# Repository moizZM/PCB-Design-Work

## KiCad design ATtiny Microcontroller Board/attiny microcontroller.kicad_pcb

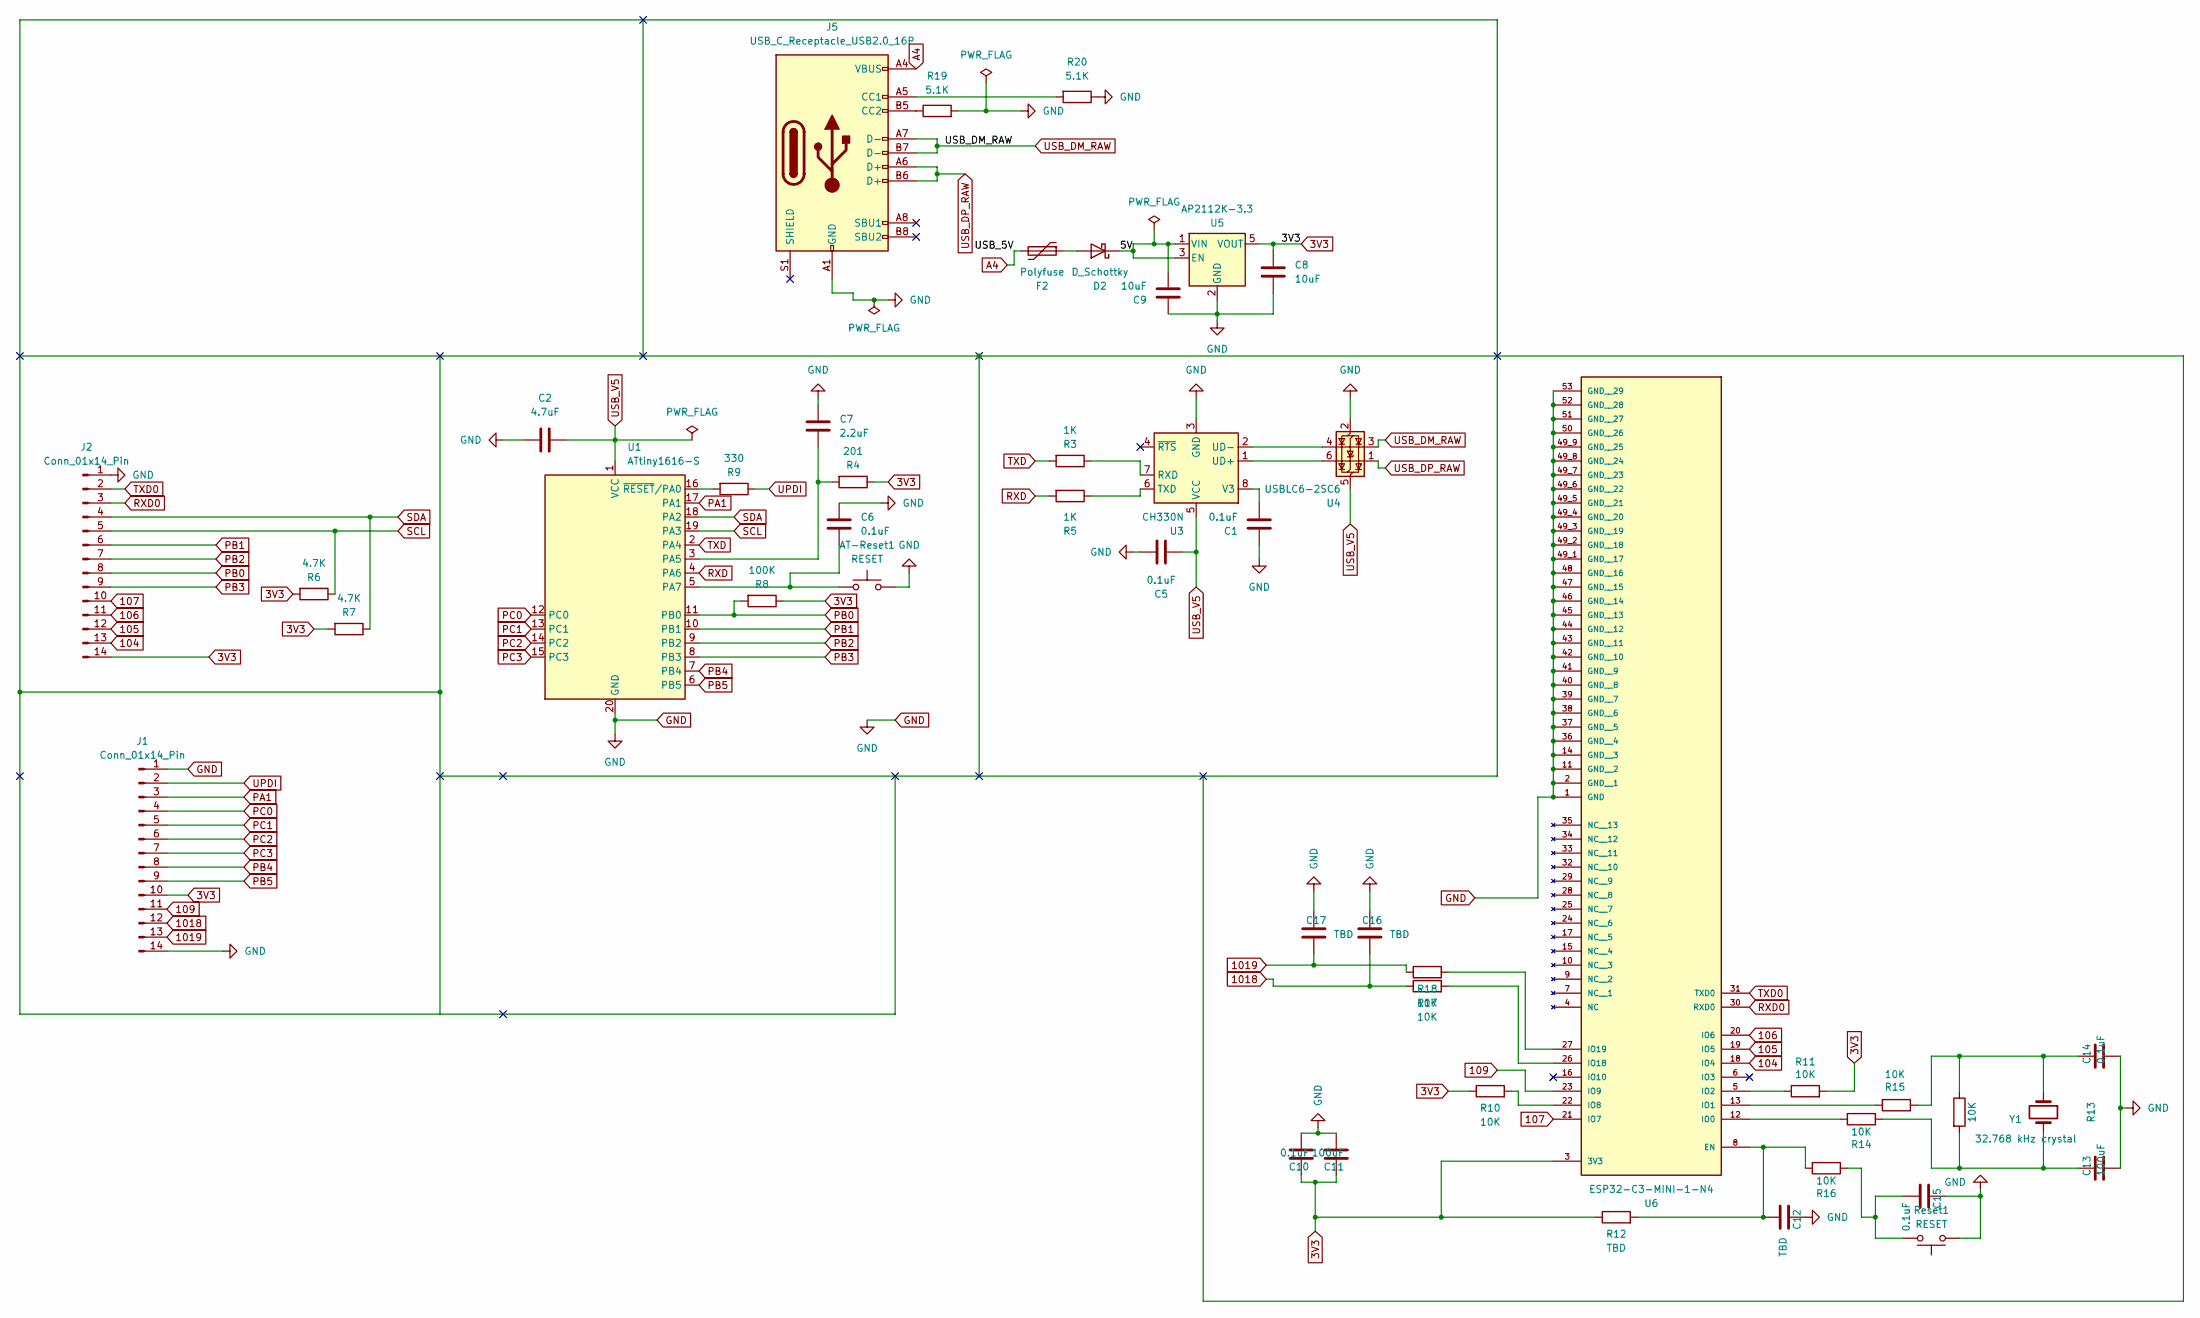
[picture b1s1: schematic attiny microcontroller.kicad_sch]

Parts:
AT-Reset1: RESET; SW_Push_SPST_NO_Alps_SKRK
C1, C5, C6, C10, C14, C15: 0.1uF; C_0201_0603Metric_Pad0.64x0.40mm_HandSolder
C2: 4.7uF; C_0201_0603Metric_Pad0.64x0.40mm_HandSolder
C7: 2.2uF; C_0201_0603Metric_Pad0.64x0.40mm_HandSolder
C8, C9: 10uF; C_0201_0603Metric_Pad0.64x0.40mm_HandSolder
C11, C13: 100uF; C_0201_0603Metric_Pad0.64x0.40mm_HandSolder
C12, C16, C17: TBD; C_0201_0603Metric_Pad0.64x0.40mm_HandSolder
D2: D_Schottky; D_2114_3652Metric
F2: Polyfuse; FUSE_MF-SM030-2_BRN
J1, J2: Conn_01x14_Pin; PinHeader_1x14_P1.00mm_Vertical
J5: USB_C_Receptacle_USB2.0_16P; USB_C_Receptacle_GCT_USB4110
R3, R5: 1K; R_0201_0603Metric
R4: 201; R_0201_0603Metric
R6, R7: 4.7K; R_0201_0603Metric
R8: 100K; R_0201_0603Metric
R9: 330; R_0201_0603Metric
R10, R11, R13, R14, R15, R16, R17, R18: 10K; R_0201_0603Metric
R12: TBD; C_0201_0603Metric_Pad0.64x0.40mm_HandSolder
R19, R20: 5.1K; R_0201_0603Metric
Reset1: RESET; SW_Push_SPST_NO_Alps_SKRK
U1: ATtiny1616-S; SOIC-20W_7.5x12.8mm_P1.27mm
U3: CH330N; SOIC-8_3.9x4.9mm_P1.27mm
U4: USBLC6-2SC6; SOT-23-6
U5: AP2112K-3.3; SOT-23-5
U6: ESP32-C3-MINI-1-N4; XCVR_ESP32-C3-MINI-1-N4; PARTREV v1.0
Y1: 32.768 kHz crystal; Crystal_SMD_3215-2Pin_3.2x1.5mm

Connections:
3V3: C8.1, C10.2, C11.2, J1.10, J2.14, R4.1, R6.2, R7.2, R8.1, R10.1, R11.2, R12.1, U5.5 (VOUT), U6.3 (3V3)
104: J2.13, U6.18 (IO4)
105: J2.12, U6.19 (IO5)
106: J2.11, U6.20 (IO6)
107: J2.10, U6.21 (IO7)
109: J1.11, U6.23 (IO9)
1018: C16.1, J1.12, R17.1
1019: C17.1, J1.13, R18.1
/5V: C9.2, D2.1 (K), U5.1 (VIN), U5.3 (EN)
A4: F2.2, J5.A4 (VBUS), J5.A9 (VBUS), J5.B4 (VBUS), J5.B9 (VBUS)
GND: AT-Reset1.2, C1.1, C2.2, C5.1, C6.2, C7.2, C8.2, C9.1, C10.1, C11.1, C12.2, C13.1, C14.1, C15.2, C16.2, C17.2, J1.1, J1.14, J2.1, J5.A1 (GND), J5.A12 (GND), J5.B1 (GND), J5.B12 (GND), R19.2, R20.1, Reset1.1, U1.20 (GND), U3.3 (GND), U4.2 (GND), U5.2 (GND), U6.1 (GND), U6.2 (GND__1), U6.11 (GND__2), U6.14 (GND__3), U6.36 (GND__4), U6.37 (GND__5), U6.38 (GND__6), U6.39 (GND__7), U6.40 (GND__8), U6.41 (GND__9), U6.42 (GND__10), U6.43 (GND__11), U6.44 (GND__12), U6.45 (GND__13), U6.46 (GND__14), U6.47 (GND__15), U6.48 (GND__16), U6.49_1 (GND__17), U6.49_2 (GND__18), U6.49_3 (GND__19), U6.49_4 (GND__20), U6.49_5 (GND__21), U6.49_6 (GND__22), U6.49_7 (GND__23), U6.49_8 (GND__24), U6.49_9 (GND__25), U6.50 (GND__26), U6.51 (GND__27), U6.52 (GND__28), U6.53 (GND__29); also elsewhere on the board
unnamed: C13.2, R13.2, R14.1, Y1.2
unnamed: C14.2, R13.1, R15.1, Y1.1
unnamed 13: C15.1, R16.1, Reset1.2; also elsewhere on the board
unnamed: D2.2 (A), F2.1
unnamed: J5.A5 (CC1), R20.2
unnamed: J5.B5 (CC2), R19.1
unnamed: C7.1, R4.2, U1.3 (PA5)
unnamed 18: AT-Reset1.1, C6.1, U1.5 (PA7); also elsewhere on the board
unnamed: R9.2, U1.16 (~RESET/PA0)
unnamed: R3.1, U3.7 (RXD)
unnamed: R5.1, U3.6 (TXD)
unnamed: U3.1 (UD+), U4.6 (I/O1)
unnamed: U3.2 (UD-), U4.4 (I/O2)
unnamed: C1.2, U3.8 (V3)
unnamed: C12.1, R12.2, R16.2, U6.8 (EN)
unnamed: R14.2, U6.12 (IO0)
unnamed: R15.2, U6.13 (IO1)
unnamed: R11.1, U6.5 (IO2)
unnamed: R10.2, U6.22 (IO8)
unnamed: R17.2, U6.26 (IO18)
unnamed: R18.2, U6.27 (IO19)
PA1: J1.3, U1.17 (PA1)
PB0: J2.8, R8.2, U1.11 (PB0)
PB1: J2.6, U1.10 (PB1)
PB2: J2.7, U1.9 (PB2)
PB3: J2.9, U1.8 (PB3)
PB4: J1.8, U1.7 (PB4)
PB5: J1.9, U1.6 (PB5)
PC0: J1.4, U1.12 (PC0)
PC1: J1.5, U1.13 (PC1)
PC2: J1.6, U1.14 (PC2)
PC3: J1.7, U1.15 (PC3)
RXD: R5.2, U1.4 (PA6)
RXD0: J2.3, U6.30 (RXD0)
SCL: J2.5, R6.1, U1.19 (PA3)
SDA: J2.4, R7.1, U1.18 (PA2)
TXD: R3.2, U1.2 (PA4)
TXD0: J2.2, U6.31 (TXD0)
UPDI: J1.2, R9.1
USB_DM_RAW: J5.A7 (D-), J5.B7 (D-), U4.3 (I/O2)
USB_DP_RAW: J5.A6 (D+), J5.B6 (D+), U4.1 (I/O1)
USB_V5: C2.1, C5.2, U1.1 (VCC), U3.5 (VCC), U4.5 (VBUS)

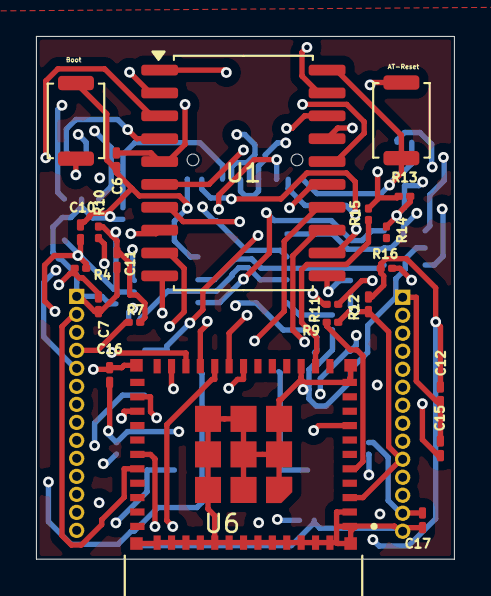
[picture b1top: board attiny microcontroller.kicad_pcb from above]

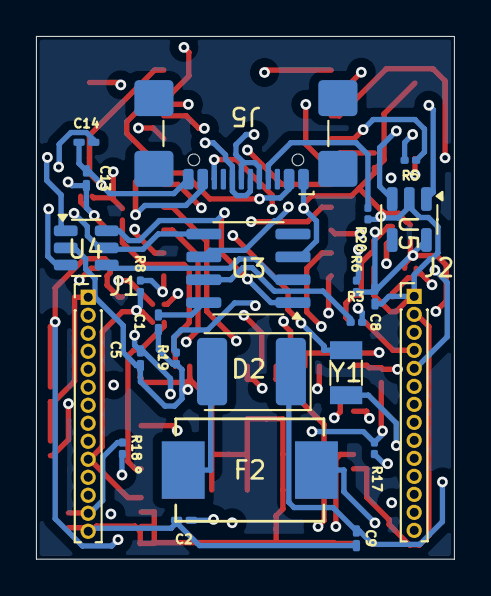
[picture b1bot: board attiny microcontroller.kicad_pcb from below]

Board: 4 copper layers, 23.2 x 29.0 mm, 46 parts (24 on the bottom side), 53 nets.

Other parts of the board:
AT-Reset: RESET; SW_Push_SPST_NO_Alps_SKRK
Boot: RESET; SW_Push_SPST_NO_Alps_SKRK

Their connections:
GND: AT-Reset.2, Boot.1; also elsewhere on the board
unnamed 13: Boot.2; also elsewhere on the board
unnamed 18: AT-Reset.1; also elsewhere on the board

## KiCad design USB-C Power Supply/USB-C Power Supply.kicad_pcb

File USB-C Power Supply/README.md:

# USB-C Power Supply
> 3D  viwe

> Layout

# USB-C Power Supply

## Overview
This project demonstrates the complete design and development of a **USB-C Power Supply** circuit.  
The goal was to create a small PCB that outputs **5 V** through a **USB Type-C** connector using correct CC (Configuration Channel) resistors.  
The board includes a power indicator LED, decoupling capacitors, and is fully ready for **JLCPCB** manufacturing.

---

## What Was Done
- Designed a **schematic** in **KiCad 8.0** for a 5 V USB-C power source.  
- Implemented **CC1** and **CC2 pull-down resistors (5.1 kΩ)** for correct USB-C negotiation.  
- Added **100 nF decoupling capacitor** for voltage stability.  
- Added **LED indicator** with **1 kΩ resistor** for power-on status.  
- Created and annotated all symbols and footprints in KiCad.  
- Designed a **two-layer PCB layout** following **JLCPCB** design rules.  
- Defined **board outline, silkscreen labels, mounting holes**, and reference text.  
- Generated **Gerber**, **Drill**, **BOM**, and **Pick-and-Place** files for fabrication.  
- Verified schematic (ERC) and layout (DRC) before manufacturing.  
- Prepared files for **JLCPCB assembly** and optional 3D-printed enclosure.

---

## Hardware Details
| Parameter | Description |
|------------|-------------|
| **Input** | USB-C Receptacle (VBUS = 5 V) |
| **Output** | 2-Pin Header (5 V / GND) |
| **Resistors** | 5.1 kΩ × 2 (CC1/CC2), 1 kΩ × 1 (LED) |
| **Capacitors** | 100 nF (Decoupling) |
| **Indicator** | Power LED |
| **Board Layers** | 2 |
| **Power** | 5 V @ up to 3 A |
| **Mounting** | 4 × M2 holes |

---

## Project Files
- `USB-C Power Supply.kicad_pro` – KiCad project file  
- `USB-C Power Supply.kicad_sch` – Schematic  
- `USB-C Power Supply.kicad_pcb` – PCB layout  
- `SCH.pdf` – Printable schematic reference  

---

## Manufacturing and Assembly
1. Export **Gerber** and **Drill** files from KiCad.  
2. Upload the ZIP archive to [**JLCPCB**](https://jlcpcb.com).  
3. Choose desired solder-mask and silkscreen colors.  
4. (Optional) Add logo or image for silkscreen layer.  
5. Order boards (with or without assembly) and test after delivery.

---

## Testing
- Connected a USB-C cable from a 5 V adapter.  
- Verified **5 V output** at the terminal header.  
- Observed **LED indicator ON** confirming active power.  
- Ensured no short circuits or trace issues.

---

## Results
The PCB provides a **stable 5 V output**, compact design, and clear labeling.  
It can serve as a reference or base module for **USB-powered embedded projects** or **sensor systems** that need a simple regulated power supply.

---

## Tools Used
- **KiCad 8.0** – Schematic capture and PCB layout  
- **JLCPCB** – PCB manufacturing and assembly  
- **Fusion 360 (optional)** – Enclosure and 3D model design  

---

## Author
**Moiz Zaheer Malik**  
Hochschule Hamm-Lippstadt (HSHL)  
October 2025

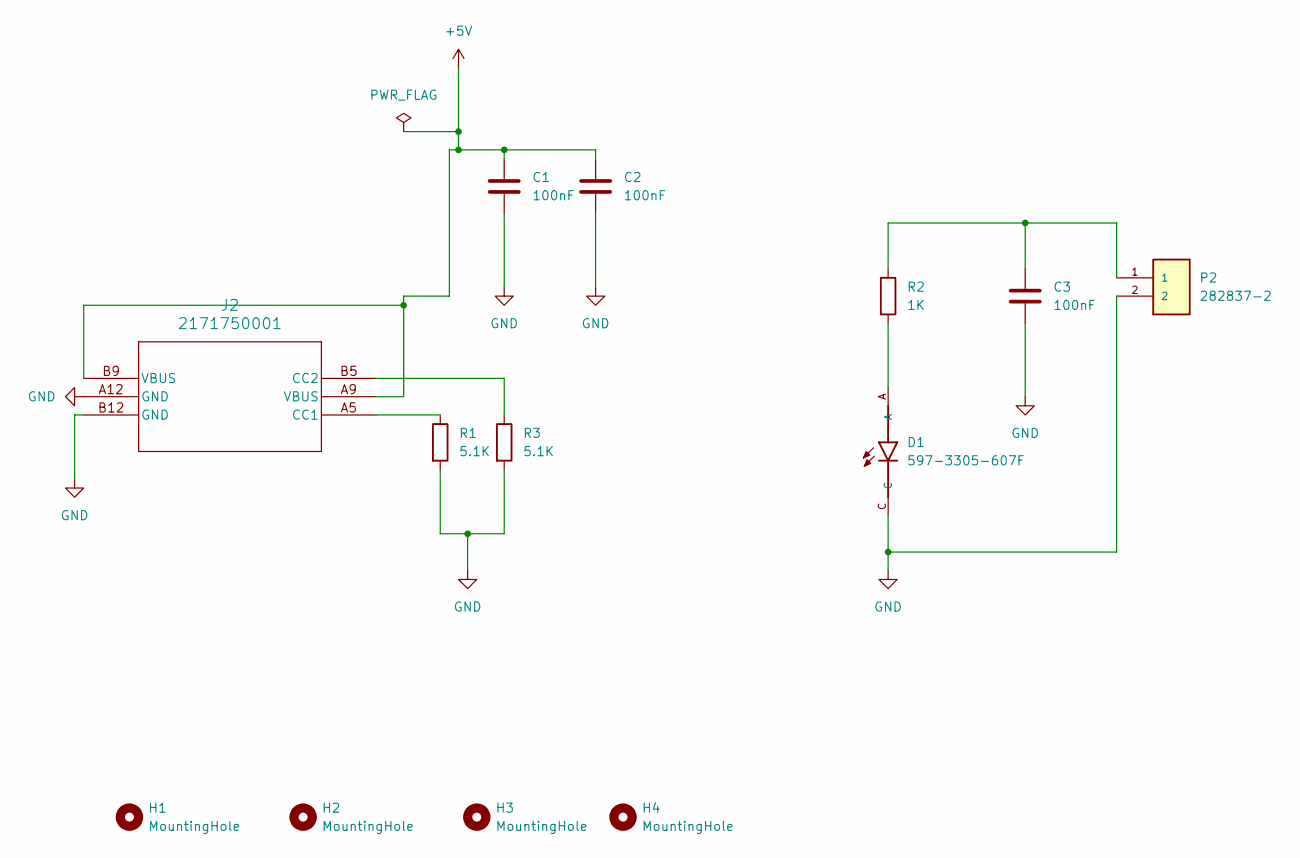
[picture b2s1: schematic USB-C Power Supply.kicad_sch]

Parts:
C1, C2, C3: 100nF; C_0201_0603Metric
D1: 597-3305-607F; LEDC2012X70N
H1, H2, H3, H4: MountingHole; MountingHole_2.2mm_M2_DIN965_Pad
J2: 2171750001; 2171750001_MOL
P2: 282837-2; TE_282837-2; PARTREV G3
R1, R3: 5.1K; R_0201_0603Metric
R2: 1K; R_0201_0603Metric

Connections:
+5V: C1.1, C2.1, J2.A9 (VBUS), J2.B9 (VBUS)
GND: C1.2, C2.2, C3.2, D1.C, J2.A12 (GND), J2.B12 (GND), P2.2, R1.2, R3.2
unnamed: C3.1, P2.1, R2.1
unnamed: D1.A, R2.2
unnamed: J2.A5 (CC1), R1.1
unnamed: J2.B5 (CC2), R3.1

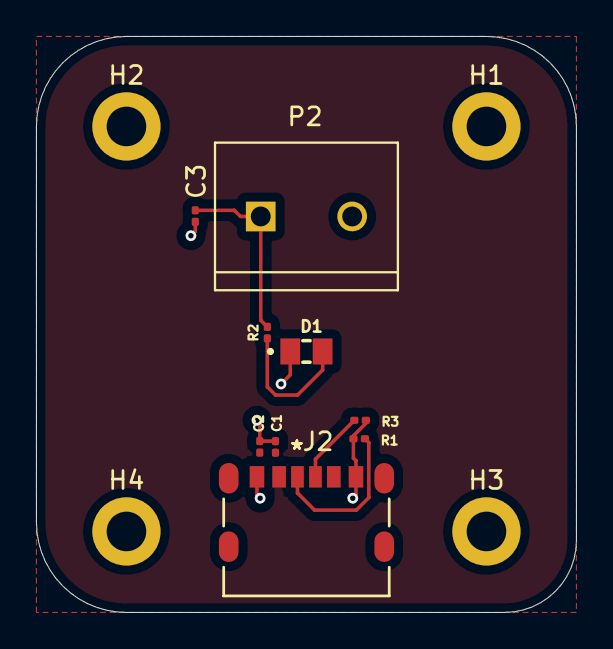
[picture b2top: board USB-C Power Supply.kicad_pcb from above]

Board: 2 copper layers, 30.0 x 32.0 mm, 13 parts (0 on the bottom side), 6 nets.

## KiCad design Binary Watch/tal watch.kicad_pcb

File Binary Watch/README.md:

# Binary Watch (ATtiny1616)

> **Inspired by:** taifur https://www.instructables.com/member/taifur/

 > [PCB Binary Watch – Instructables](https://www.instructables.com/PCB-Binary-Watch/)

This project is a **Binary Digital Watch** designed in **KiCad** using an **ATtiny1616** microcontroller.  
It displays the time using LEDs arranged in binary form, powered by a coin-cell battery and driven by a real-time clock (RTC).

---

##  Overview
- **MCU:** ATtiny1616 (AVR 0-series)
- **Power Source:** CR2032 coin-cell battery
- **Display:** 13 LEDs (binary representation of hours and minutes)
- **Resistors:** Current-limiting for LED control
- **Clock:** External RTC for accurate timekeeping
- **PCB:** 2-layer FR-4 board, compact circular layout for wristwatch form factor

---

##  Circuit Highlights
- The LEDs are arranged in groups:
  - **Hours (1–12)** → 4 LEDs (binary)
  - **Minutes (0–59)** → 6 LEDs (binary)
  - Controlled via GPIO pins of the ATtiny1616.
- **Resistors** limit LED current to protect the MCU pins.
- **Coin-cell holder (U4)** provides power and acts as the mechanical base.
- **UPDI header** included for programming the microcontroller.

---

##  PCB Design
- Designed and routed in **KiCad 8**.
- Features:
  - Front copper layer: signal traces and LED anodes.
  - Back copper layer: ground pour (GND).
  - Thermal reliefs for soldering.
  - Tented vias to avoid solder mask shorts.
- Optimized for low current draw and minimal power loss.

---

##  Fabrication Settings
| Parameter | Value |
|------------|--------|
| Layers | 2 |
| Material | FR-4 |
| Thickness | 1.6 mm |
| Finish | HASL-Lead-Free |
| Min track/space | 0.2 mm |
| Via | 0.6 mm / 0.3 mm drill |
| Solder mask | Green |
| Silkscreen | White |

---

##  Assembly & Testing
1. Program ATtiny1616 via **UPDI** interface.
2. Verify RTC communication and LED output sequence.
3. Insert CR2032 cell and confirm LED time display pattern.
4. Measure current draw to ensure low-power standby operation.

---

##  Files
- `Binary Watch.kicad_sch` — complete schematic  
- `Binary Watch.kicad_pcb` — routed PCB layout  
- `BOM.csv` — parts list for fabrication and assembly  

---

##  Future Improvements
- Add button input for time-setting.
- Integrate charging circuit for Li-ion coin cell.
- Add low-power sleep and wake functions in firmware.

---

### Author
Designed by **Moiz Zaheer Malik**  
Location: **Lippstadt, Germany**

---

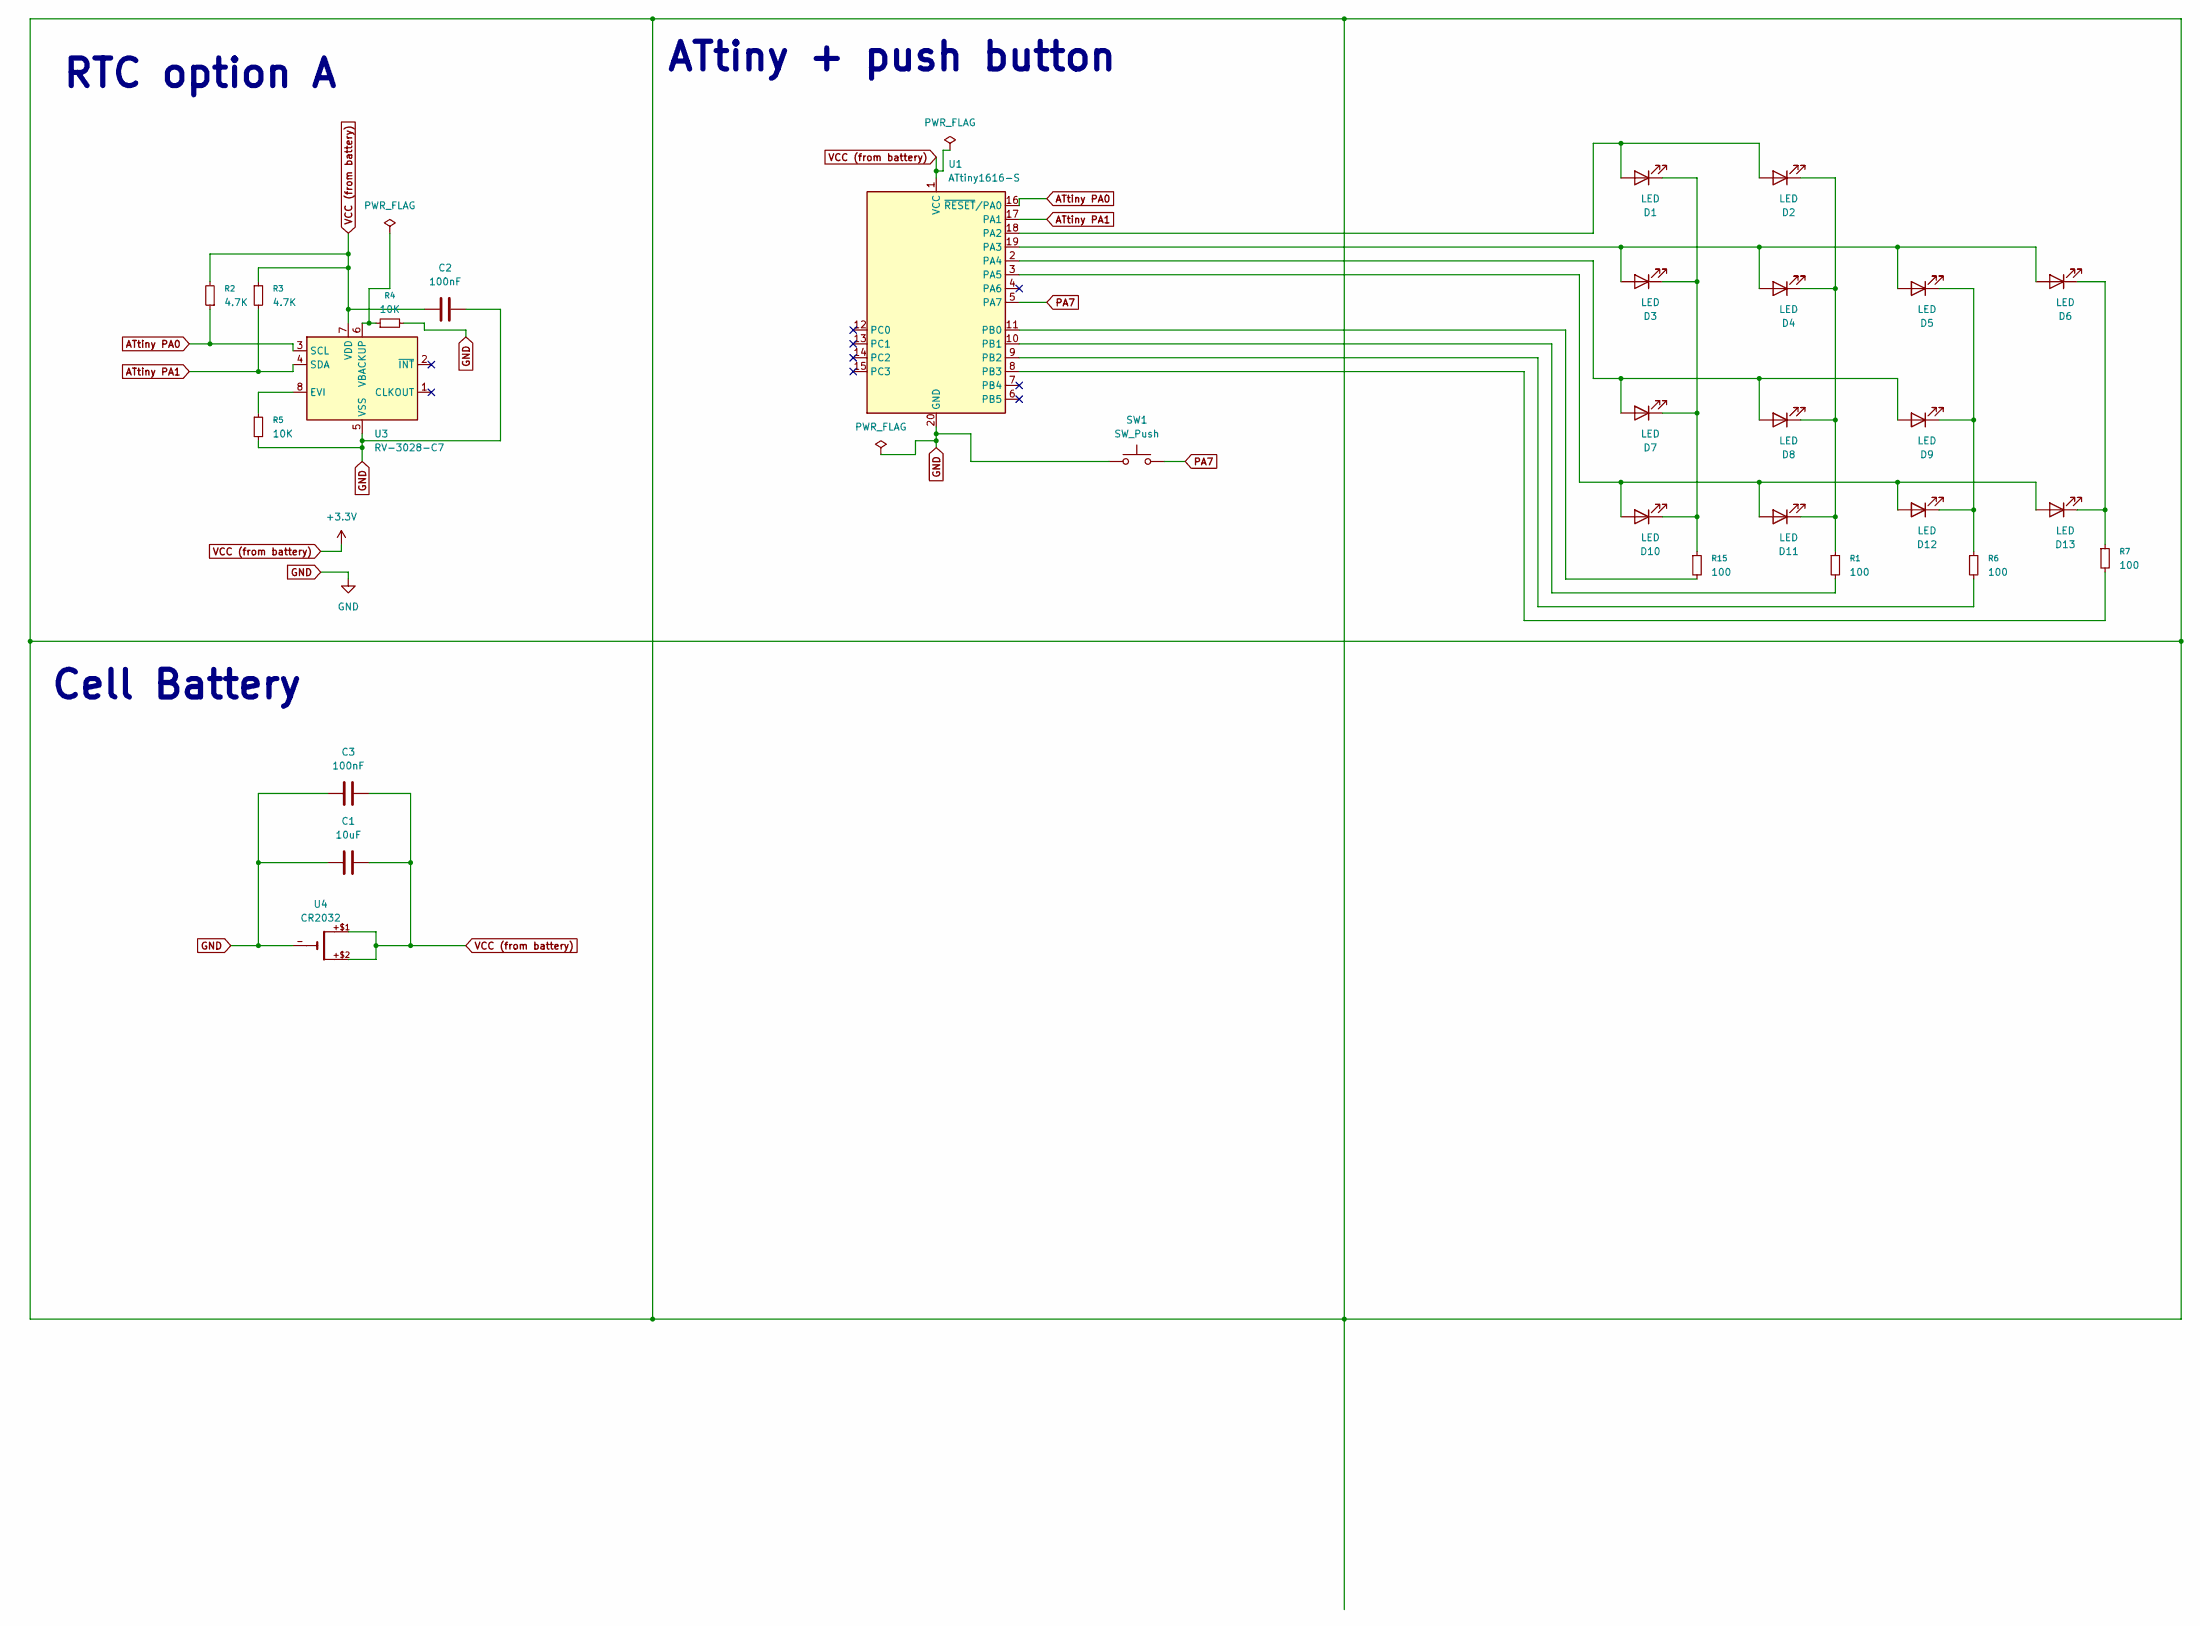
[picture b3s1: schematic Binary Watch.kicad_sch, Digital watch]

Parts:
C1: 10uF; C_0201_0603Metric
C2, C3: 100nF; C_0201_0603Metric
D1, D2, D3, D4, D5, D6, D7, D8, D9, D10, D11, D12, D13: LED; LED_Kingbright_AAA3528ESGCT
R1, R6, R7, R15: 100; R_0201_0603Metric
R2, R3: 4.7K; R_0201_0603Metric
R4, R5: 10K; R_0201_0603Metric
SW1: SW_Push; SW_SPST_PTS810
U1: ATtiny1616-S; SOIC-20W_7.5x12.8mm_P1.27mm
U3: RV-3028-C7; MicroCrystal_C7_SON-8_1.5x3.2mm_P0.9mm
U4: CR2032; CR2032-SMD

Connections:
ATtiny PA0: R2.1, U1.16 (~RESET/PA0), U3.3 (SCL)
ATtiny PA1: R3.2, U1.17 (PA1), U3.4 (SDA)
GND: C1.2, C2.1, C3.2, R4.2, R5.2, SW1.1, U1.20 (GND), U3.5 (VSS), U4.-
unnamed: D1.2 (A), D2.2 (A), U1.18 (PA2)
unnamed: D1.1 (K), D3.1 (K), D7.1 (K), D10.1 (K), R15.1
unnamed: D3.2 (A), D4.2 (A), D5.2 (A), D6.2 (A), U1.19 (PA3)
unnamed: D7.2 (A), D8.2 (A), D9.2 (A), U1.2 (PA4)
unnamed: D10.2 (A), D11.2 (A), D12.2 (A), D13.2 (A), U1.3 (PA5)
unnamed: D2.1 (K), D4.1 (K), D8.1 (K), D11.1 (K), R1.1
unnamed: D5.1 (K), D9.1 (K), D12.1 (K), R6.1
unnamed: D6.1 (K), D13.1 (K), R7.1
unnamed: R15.2, U1.11 (PB0)
unnamed: R1.2, U1.10 (PB1)
unnamed: R6.2, U1.9 (PB2)
unnamed: R7.2, U1.8 (PB3)
unnamed: R5.1, U3.8 (EVI)
unnamed: R4.1, U3.6 (VBACKUP)
PA7: SW1.2, U1.5 (PA7)
VCC (from battery): C1.1, C2.2, C3.1, R2.2, R3.1, U1.1 (VCC), U3.7 (VDD), U4.+$1, U4.+$2

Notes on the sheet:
ATtiny + push button
RTC option A
Cell Battery

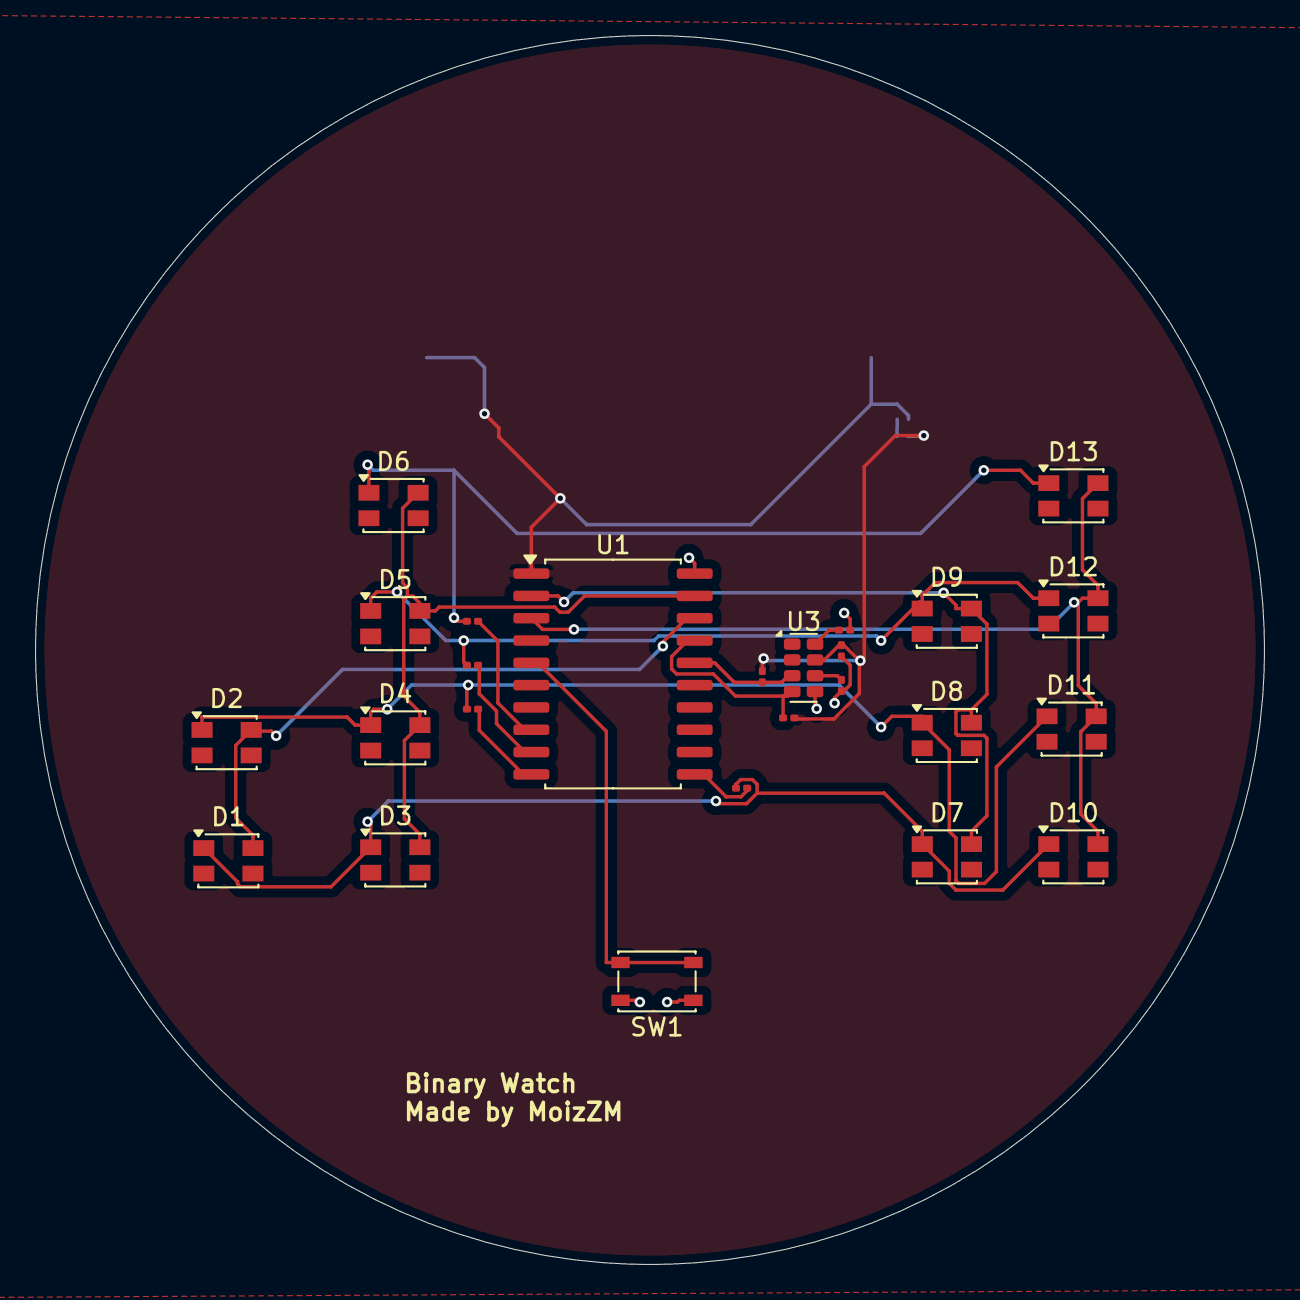
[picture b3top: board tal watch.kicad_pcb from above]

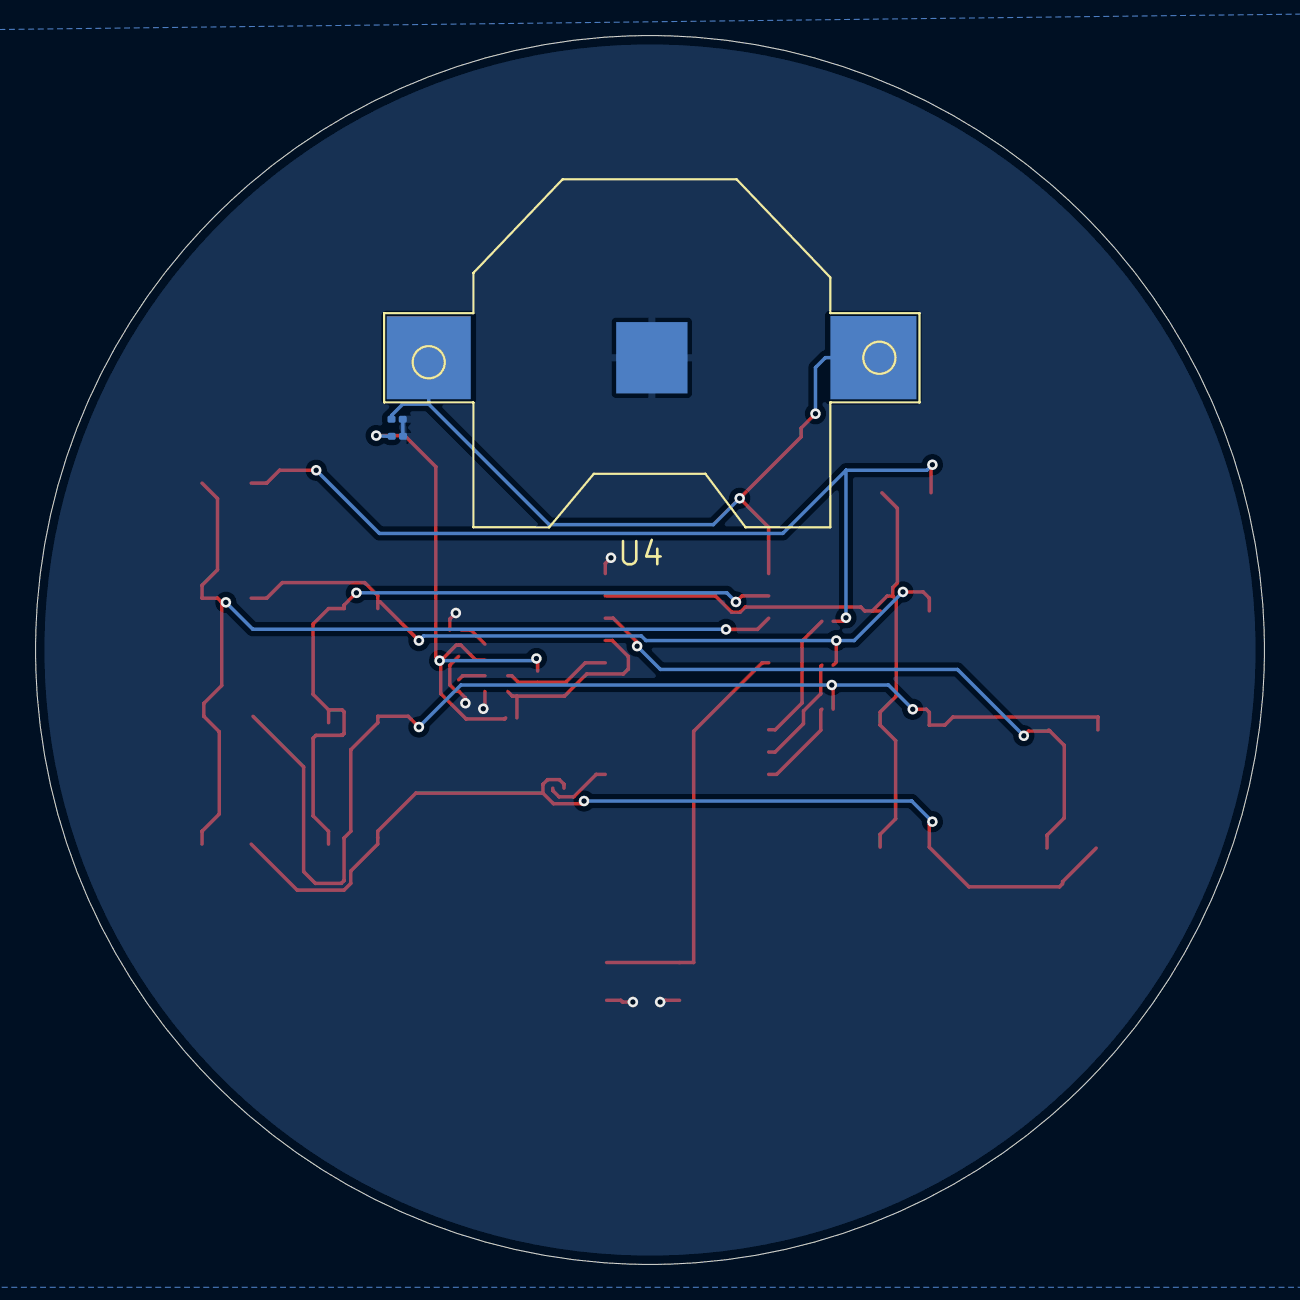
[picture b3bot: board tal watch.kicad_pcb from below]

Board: 2 copper layers, 70.0 x 70.0 mm, 28 parts (3 on the bottom side), 19 nets.
